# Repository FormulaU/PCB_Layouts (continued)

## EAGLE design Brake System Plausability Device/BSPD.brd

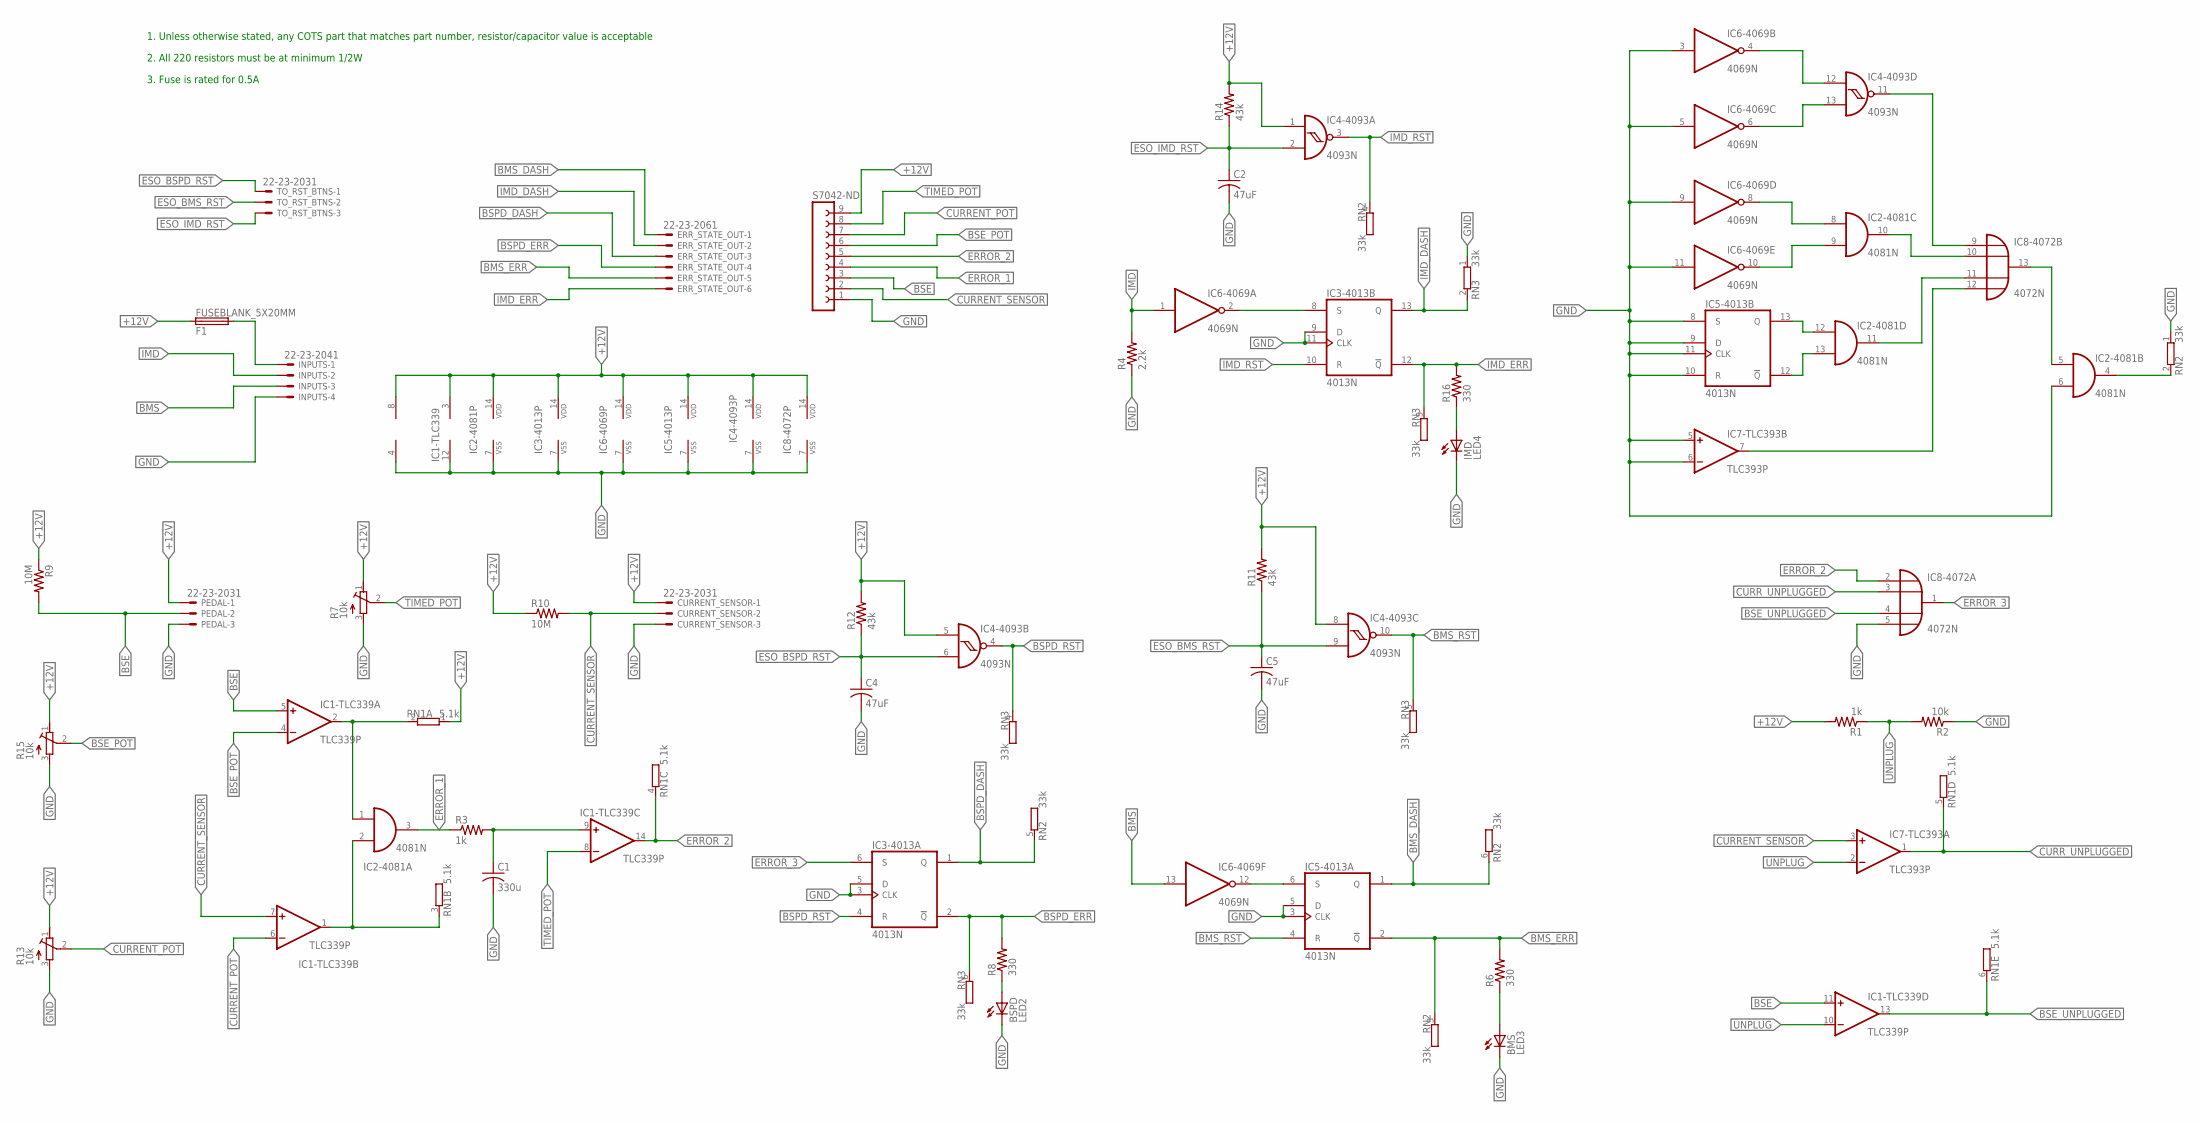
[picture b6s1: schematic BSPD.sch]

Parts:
BMS: LED3; LED3MM
BSPD: LED2; LED3MM
C1: 330u; C225-108X268
C2, C4, C5: 47uF; C050-024X044
CURRENT_SENSOR: 22-23-2031
ERR_STATE_OUT: 22-23-2061
F1: FUSEBLANK_5X20MM; FUSE_HOLDER_5X20MM
IC1-TLC339: TLC339P; DIL14
IC2-4081: 4081N; DIL14
IC3-4013, IC5-4013: 4013N; DIL14
IC4-4093: 4093N; DIL14
IC6-4069: 4069N; DIL14
IC7-TLC393: TLC393P; DIL08
IC8-4072: 4072N; DIL14
IMD: LED4; LED3MM
INPUTS: 22-23-2041
PEDAL: 22-23-2031
R1, R3: 1k; 0207/12
R2: 10k; 0207/12
R4: 2.2k; 0207/12
R6, R8, R16: 330; 0207/12
R7, R13, R15: 10k; RTRIM3006P
R9, R10: 10M; 0207/12
R11, R12, R14: 43k; 0207/12
RN1: 5.1k; SIL6
RN2, RN3: 33k; SIL6
S7042-ND: FE09W
TO_RST_BTNS: 22-23-2031

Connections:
+12V: CURRENT_SENSOR.1, F1.1, IC1-TLC339.3 (V+), IC2-4081.14 (VDD), IC3-4013.14 (VDD), IC4-4093.1 (I0), IC4-4093.5 (I0), IC4-4093.8 (I0), IC4-4093.14 (VDD), IC5-4013.14 (VDD), IC6-4069.14 (VDD), IC7-TLC393.8 (V+), IC8-4072.14 (VDD), PEDAL.1, R1.2, R7.1 (E), R9.1, R10.1, R11.2, R12.2, R13.1 (E), R14.2, R15.1 (E), RN1.1, S7042-ND.9
BMS: IC6-4069.13 (I), INPUTS.3
BMS_DASH: ERR_STATE_OUT.1, IC5-4013.1 (Q), RN2.6 (2)
BMS_ERR: ERR_STATE_OUT.5, IC5-4013.2 (!Q), R6.2, RN2.3 (2)
BMS_RST: IC4-4093.10 (O), IC5-4013.4 (R), RN3.5 (2)
BSE: IC1-TLC339.5 (+IN), IC1-TLC339.11 (+IN), PEDAL.2, R9.2, S7042-ND.3
BSE_POT: IC1-TLC339.4 (-IN), R15.2 (S), S7042-ND.6
BSE_UNPLUGGED: IC1-TLC339.13 (OUT), IC8-4072.4 (I2), RN1.6 (2)
BSPD_DASH: ERR_STATE_OUT.3, IC3-4013.1 (Q), RN2.5 (2)
BSPD_ERR: ERR_STATE_OUT.4, IC3-4013.2 (!Q), R8.2, RN3.6 (2)
BSPD_RST: IC3-4013.4 (R), IC4-4093.4 (O), RN3.4 (2)
CURRENT_POT: IC1-TLC339.6 (-IN), R13.2 (S), S7042-ND.7
CURRENT_SENSOR: CURRENT_SENSOR.2, IC1-TLC339.7 (+IN), IC7-TLC393.3 (+IN), R10.2, S7042-ND.2
CURR_UNPLUGGED: IC7-TLC393.1 (OUT), IC8-4072.3 (I1), RN1.5 (2)
ERROR_1: IC2-4081.3 (O), R3.1, S7042-ND.4
ERROR_2: IC1-TLC339.14 (OUT), IC8-4072.2 (I0), RN1.4 (2), S7042-ND.5
ERROR_3: IC3-4013.6 (S), IC8-4072.1 (O)
ESO_BMS_RST: C5.1, IC4-4093.9 (I1), R11.1, TO_RST_BTNS.2
ESO_BSPD_RST: C4.1, IC4-4093.6 (I1), R12.1, TO_RST_BTNS.1
ESO_IMD_RST: C2.1, IC4-4093.2 (I1), R14.1, TO_RST_BTNS.3
GND: BMS.K (C), BSPD.K (C), C1.2, C2.2, C4.2, C5.2, CURRENT_SENSOR.3, IC1-TLC339.12 (V-), IC2-4081.6 (I1), IC2-4081.7 (VSS), IC3-4013.3 (CLK), IC3-4013.5 (D), IC3-4013.7 (VSS), IC3-4013.9 (D), IC3-4013.11 (CLK), IC4-4093.7 (VSS), IC5-4013.3 (CLK), IC5-4013.5 (D), IC5-4013.7 (VSS), IC5-4013.8 (S), IC5-4013.9 (D), IC5-4013.10 (R), IC5-4013.11 (CLK), IC6-4069.3 (I), IC6-4069.5 (I), IC6-4069.7 (VSS), IC6-4069.9 (I), IC6-4069.11 (I), IC7-TLC393.4 (V-), IC7-TLC393.5 (+IN), IC7-TLC393.6 (-IN), IC8-4072.5 (I3), IC8-4072.7 (VSS), IMD.K (C), INPUTS.4, PEDAL.3, R2.1, R4.1, R7.3 (A), R13.3 (A), R15.3 (A), RN2.1, RN3.1, S7042-ND.1
IMD: IC6-4069.1 (I), INPUTS.2, R4.2
IMD_DASH: ERR_STATE_OUT.2, IC3-4013.13 (Q), RN3.2
IMD_ERR: ERR_STATE_OUT.6, IC3-4013.12 (!Q), R16.2, RN3.3 (2)
IMD_RST: IC3-4013.10 (R), IC4-4093.3 (O), RN2.4 (2)
unnamed: IC1-TLC339.2 (OUT), IC2-4081.1 (I0), RN1.2
unnamed: IC1-TLC339.1 (OUT), IC2-4081.2 (I1), RN1.3 (2)
unnamed: F1.2, INPUTS.1
unnamed: IC3-4013.8 (S), IC6-4069.2 (O)
unnamed: C1.1, IC1-TLC339.9 (+IN), R3.2
unnamed: IC7-TLC393.7 (OUT), IC8-4072.12 (I3)
unnamed: IC4-4093.11 (O), IC8-4072.9 (I0)
unnamed: BMS.A, R6.1
unnamed: IC4-4093.12 (I0), IC6-4069.4 (O)
unnamed: IC2-4081.10 (O), IC8-4072.10 (I1)
unnamed: IC2-4081.11 (O), IC8-4072.11 (I2)
unnamed: IC4-4093.13 (I1), IC6-4069.6 (O)
unnamed: IC5-4013.6 (S), IC6-4069.12 (O)
unnamed: IMD.A, R16.1
unnamed: IC2-4081.9 (I1), IC6-4069.10 (O)
unnamed: IC2-4081.8 (I0), IC6-4069.8 (O)
unnamed: IC2-4081.5 (I0), IC8-4072.13 (O)
unnamed: BSPD.A, R8.1
unnamed: IC2-4081.12 (I0), IC5-4013.13 (Q)
unnamed: IC2-4081.13 (I1), IC5-4013.12 (!Q)
unnamed: IC2-4081.4 (O), RN2.2
TIMED_POT: IC1-TLC339.8 (-IN), R7.2 (S), S7042-ND.8
UNPLUG: IC1-TLC339.10 (-IN), IC7-TLC393.2 (-IN), R1.1, R2.2

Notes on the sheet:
IC1-TLC339
1. Unless otherwise stated, any COTS part that matches part number, resistor/capacitor value is acceptable
2. All 220 resistors must be at minimum 1/2W
3. Fuse is rated for 0.5A

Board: 2 copper layers, 40 parts (0 on the bottom side), 48 nets, no tracks yet.

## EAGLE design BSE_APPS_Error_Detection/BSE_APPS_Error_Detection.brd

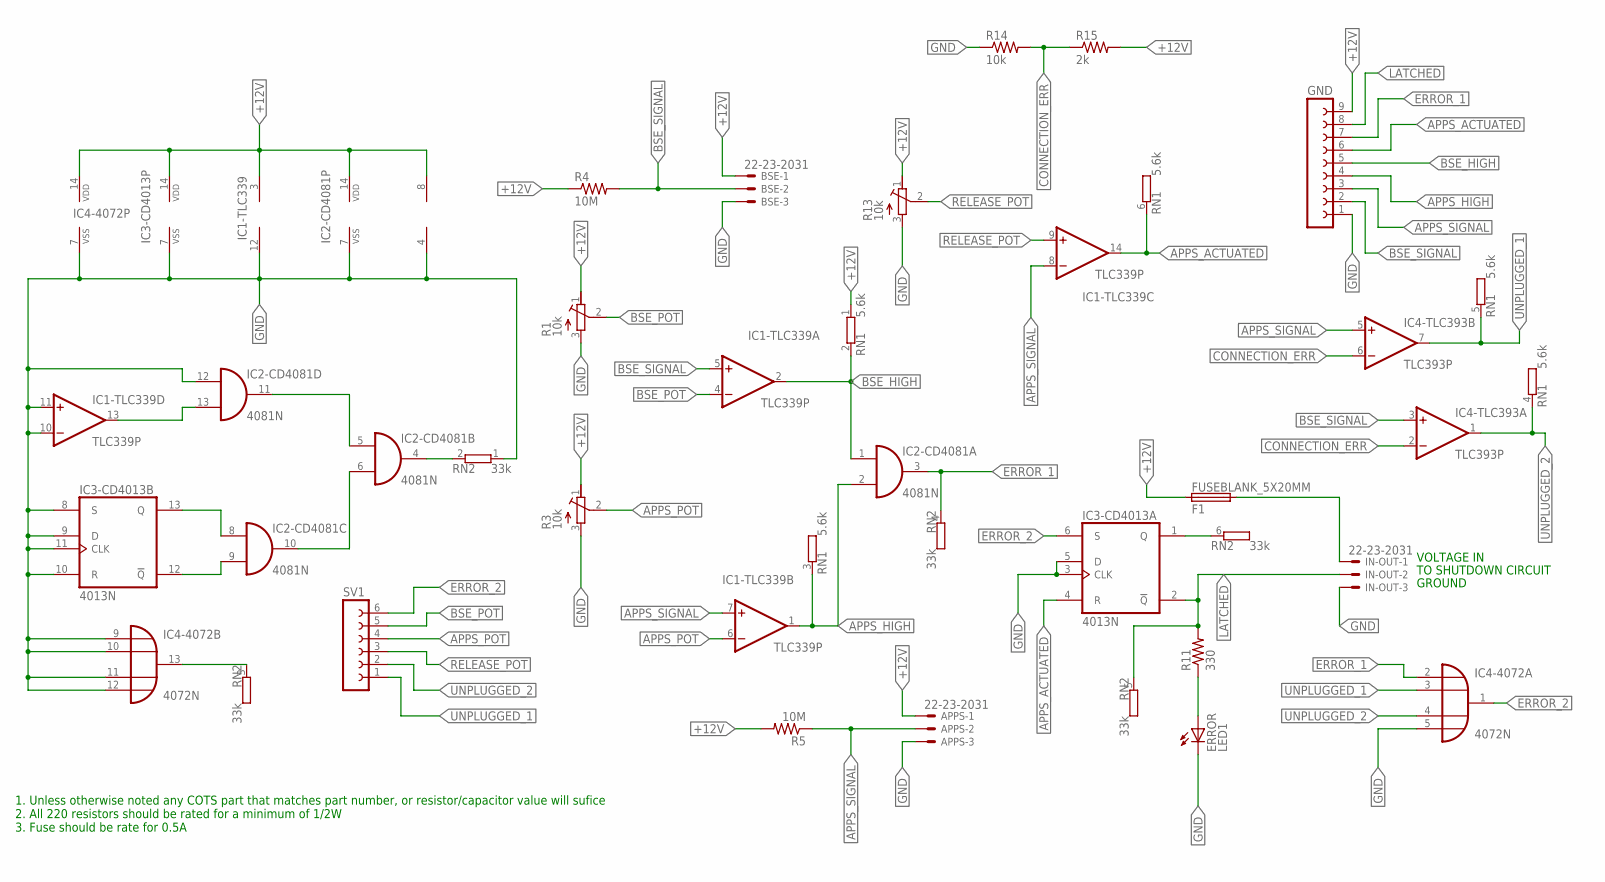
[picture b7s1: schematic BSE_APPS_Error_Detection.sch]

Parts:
APPS: 22-23-2031
BSE: 22-23-2031
ERROR: LED1; LED5MM
F1: FUSEBLANK_5X20MM; FUSE_HOLDER_5X20MM
GND: FE09W
IC1-TLC339: TLC339P; DIL14
IC2-CD4081: 4081N; DIL14
IC3-CD4013: 4013N; DIL14
IC4-4072: 4072N; DIL14
IC4-TLC393: TLC393P; DIL08
IN-OUT: 22-23-2031
R1, R3, R13: 10k; RTRIM3006P
R4, R5: 10M; 0207/10
R11: 330; 0207/10
R14: 10k; 0207/10
R15: 2k; 0207/10
RN1: 5.6k; SIL6
RN2: 33k; SIL6
SV1: FE06W

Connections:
+12V: APPS.1, BSE.1, F1.1, GND.9, IC1-TLC339.3 (V+), IC2-CD4081.14 (VDD), IC3-CD4013.14 (VDD), IC4-4072.14 (VDD), IC4-TLC393.8 (V+), R1.1 (E), R3.1 (E), R4.1, R5.2, R13.1 (E), R15.2, RN1.1
APPS_ACTUATED: GND.6, IC1-TLC339.14 (OUT), IC3-CD4013.4 (R), RN1.6 (2)
APPS_HIGH: GND.4, IC1-TLC339.1 (OUT), IC2-CD4081.2 (I1), RN1.3 (2)
APPS_POT: IC1-TLC339.6 (-IN), R3.2 (S), SV1.4
APPS_SIGNAL: APPS.2, GND.3, IC1-TLC339.7 (+IN), IC1-TLC339.8 (-IN), IC4-TLC393.5 (+IN), R5.1
BSE_HIGH: GND.5, IC1-TLC339.2 (OUT), IC2-CD4081.1 (I0), RN1.2
BSE_POT: IC1-TLC339.4 (-IN), R1.2 (S), SV1.5
BSE_SIGNAL: BSE.2, GND.2, IC1-TLC339.5 (+IN), IC4-TLC393.3 (+IN), R4.2
CONNECTION_ERR: IC4-TLC393.2 (-IN), IC4-TLC393.6 (-IN), R14.2, R15.1
ERROR_1: GND.7, IC2-CD4081.3 (O), IC4-4072.2 (I0), RN2.4 (2)
ERROR_2: IC3-CD4013.6 (S), IC4-4072.1 (O), SV1.6
GND: APPS.3, BSE.3, ERROR.K (C), GND.1, IC1-TLC339.10 (-IN), IC1-TLC339.11 (+IN), IC1-TLC339.12 (V-), IC2-CD4081.7 (VSS), IC2-CD4081.12 (I0), IC3-CD4013.3 (CLK), IC3-CD4013.5 (D), IC3-CD4013.7 (VSS), IC3-CD4013.8 (S), IC3-CD4013.9 (D), IC3-CD4013.10 (R), IC3-CD4013.11 (CLK), IC4-4072.5 (I3), IC4-4072.7 (VSS), IC4-4072.9 (I0), IC4-4072.10 (I1), IC4-4072.11 (I2), IC4-4072.12 (I3), IC4-TLC393.4 (V-), IN-OUT.3, R1.3 (A), R3.3 (A), R13.3 (A), R14.1, RN2.1
LATCHED: GND.8, IC3-CD4013.2 (!Q), IN-OUT.2, R11.2, RN2.5 (2)
unnamed: IC2-CD4081.6 (I1), IC2-CD4081.10 (O)
unnamed: IC1-TLC339.13 (OUT), IC2-CD4081.13 (I1)
unnamed: IC3-CD4013.1 (Q), RN2.6 (2)
unnamed: F1.2, IN-OUT.1
unnamed: IC2-CD4081.8 (I0), IC3-CD4013.13 (Q)
unnamed: ERROR.A, R11.1
unnamed: IC2-CD4081.9 (I1), IC3-CD4013.12 (!Q)
unnamed: IC2-CD4081.5 (I0), IC2-CD4081.11 (O)
unnamed: IC2-CD4081.4 (O), RN2.2
unnamed: IC4-4072.13 (O), RN2.3 (2)
RELEASE_POT: IC1-TLC339.9 (+IN), R13.2 (S), SV1.3
UNPLUGGED_1: IC4-4072.3 (I1), IC4-TLC393.7 (OUT), RN1.5 (2), SV1.1
UNPLUGGED_2: IC4-4072.4 (I2), IC4-TLC393.1 (OUT), RN1.4 (2), SV1.2

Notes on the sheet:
TO SHUTDOWN CIRCUIT
VOLTAGE IN
GROUND
IC1-TLC339
1. Unless otherwise noted any COTS part that matches part number, or resistor/capacitor value will sufice 2. All 220 resistors should be rated for a minimum of 1/2W 3. Fuse should be rate for 0.5A

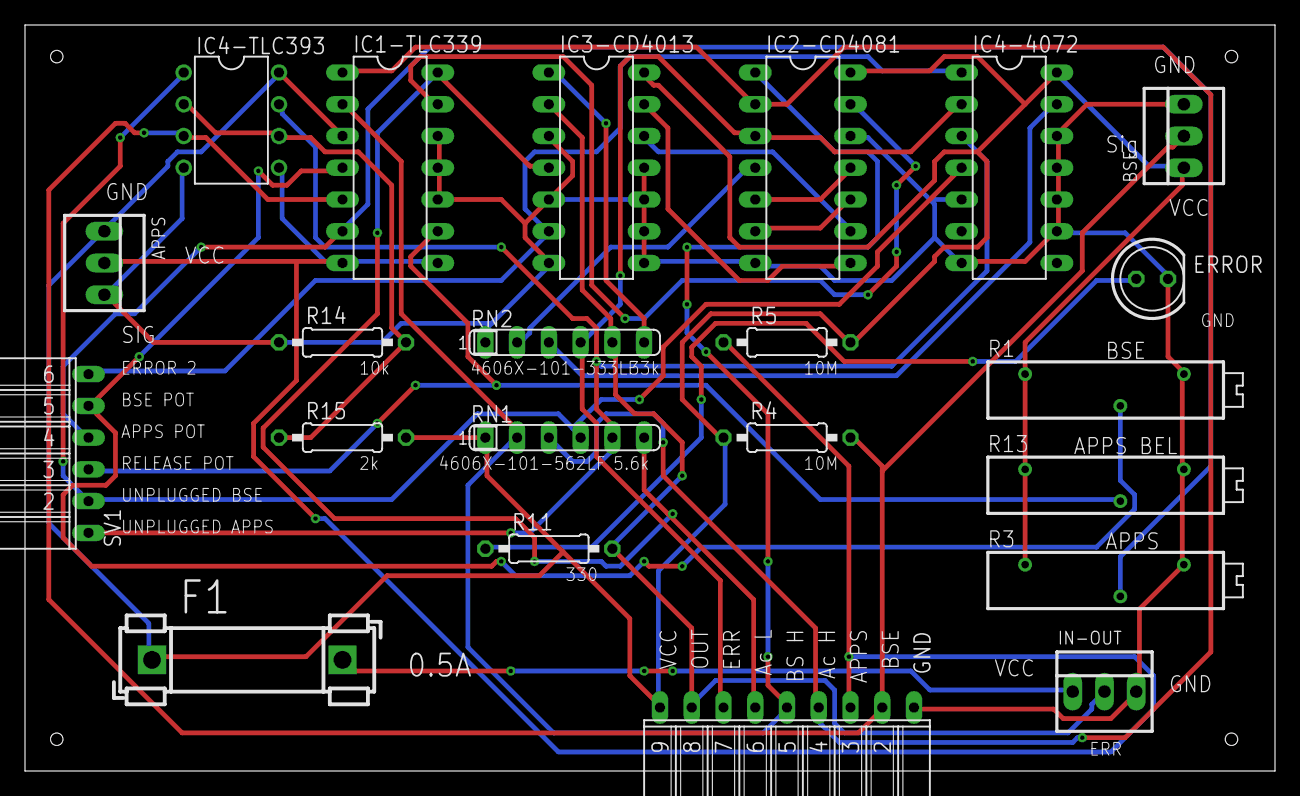
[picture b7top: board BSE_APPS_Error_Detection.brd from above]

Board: 2 copper layers, 100.0 x 59.7 mm, 22 parts (0 on the bottom side), 26 nets.

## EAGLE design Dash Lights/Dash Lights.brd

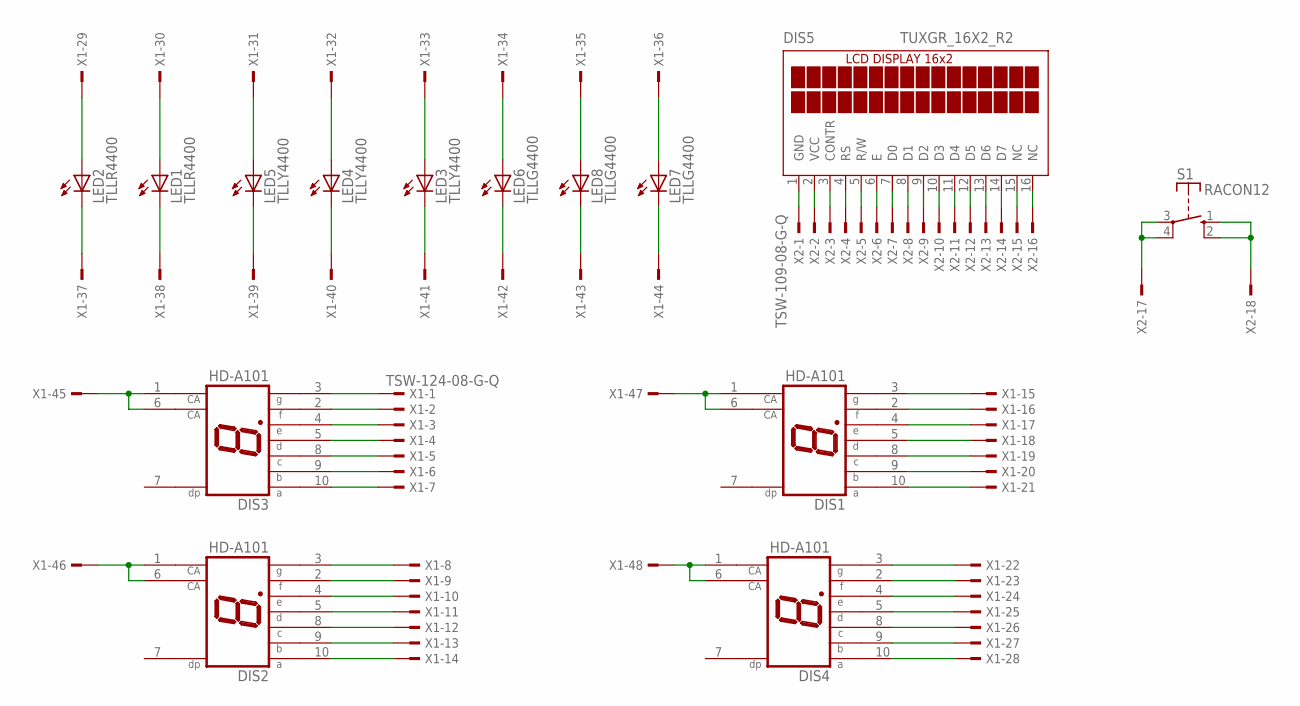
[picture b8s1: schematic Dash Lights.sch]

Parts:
DIS1, DIS2, DIS3, DIS4: HD-A101; HDSP-A
DIS5: TUXGR_16X2_R2
LED1, LED2: TLLR4400; LED3MM
LED3, LED4, LED5: TLLY4400; LED3MM
LED6, LED7, LED8: TLLG4400; LED3MM
S1: RACON12
X1: TSW-124-08-G-Q; TSW-124-XX-G-Q
X2: TSW-109-08-G-Q; TSW-109-XX-G-Q

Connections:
unnamed: DIS3.3 (G), X1.1
unnamed: DIS3.2 (F), X1.2
unnamed: DIS3.4 (E), X1.3
unnamed: DIS3.5 (D), X1.4
unnamed: DIS3.8 (C), X1.5
unnamed: DIS3.9 (B), X1.6
unnamed: DIS3.10 (A), X1.7
unnamed: DIS2.3 (G), X1.8
unnamed: DIS2.2 (F), X1.9
unnamed: DIS2.4 (E), X1.10
unnamed: DIS2.5 (D), X1.11
unnamed: DIS2.8 (C), X1.12
unnamed: DIS2.9 (B), X1.13
unnamed: DIS2.10 (A), X1.14
unnamed: DIS1.3 (G), X1.15
unnamed: DIS1.2 (F), X1.16
unnamed: DIS1.4 (E), X1.17
unnamed: DIS1.5 (D), X1.18
unnamed: DIS1.8 (C), X1.19
unnamed: DIS1.9 (B), X1.20
unnamed: DIS1.10 (A), X1.21
unnamed: DIS4.3 (G), X1.22
unnamed: DIS4.2 (F), X1.23
unnamed: DIS4.4 (E), X1.24
unnamed: DIS4.5 (D), X1.25
unnamed: DIS4.8 (C), X1.26
unnamed: DIS4.9 (B), X1.27
unnamed: DIS4.10 (A), X1.28
unnamed: LED2.A, X1.29
unnamed: LED2.K (C), X1.37
unnamed: LED1.K (C), X1.38
unnamed: LED1.A, X1.30
unnamed: LED5.A, X1.31
unnamed: LED5.K (C), X1.39
unnamed: LED4.A, X1.32
unnamed: LED4.K (C), X1.40
unnamed: LED3.K (C), X1.41
unnamed: LED3.A, X1.33
unnamed: LED6.A, X1.34
unnamed: LED6.K (C), X1.42
unnamed: LED8.K (C), X1.43
unnamed: LED7.K (C), X1.44
unnamed: LED7.A, X1.36
unnamed: LED8.A, X1.35
unnamed: DIS3.1 (CA), DIS3.6 (CA), X1.45
unnamed: DIS2.1 (CA), DIS2.6 (CA), X1.46
unnamed: DIS1.1 (CA), DIS1.6 (CA), X1.47
unnamed: DIS5.1 (GND), X2.1
unnamed: DIS5.2 (VCC), X2.2
unnamed: DIS5.3 (CONTR), X2.3
unnamed: DIS4.1 (CA), DIS4.6 (CA), X1.48
unnamed: DIS5.4 (RS), X2.4
unnamed: DIS5.5 (R/W), X2.5
unnamed: DIS5.6 (E), X2.6
unnamed: DIS5.7 (D0), X2.7
unnamed: DIS5.8 (D1), X2.8
unnamed: DIS5.9 (D2), X2.9
unnamed: DIS5.10 (D3), X2.10
unnamed: DIS5.11 (D4), X2.11
unnamed: DIS5.12 (D5), X2.12
unnamed: DIS5.13 (D6), X2.13
unnamed: DIS5.14 (D7), X2.14
unnamed: DIS5.15 (NC), X2.15
unnamed: DIS5.16 (NC), X2.16
unnamed: S1.3, S1.4, X2.17
unnamed: S1.1 (S), S1.2 (S), X2.18

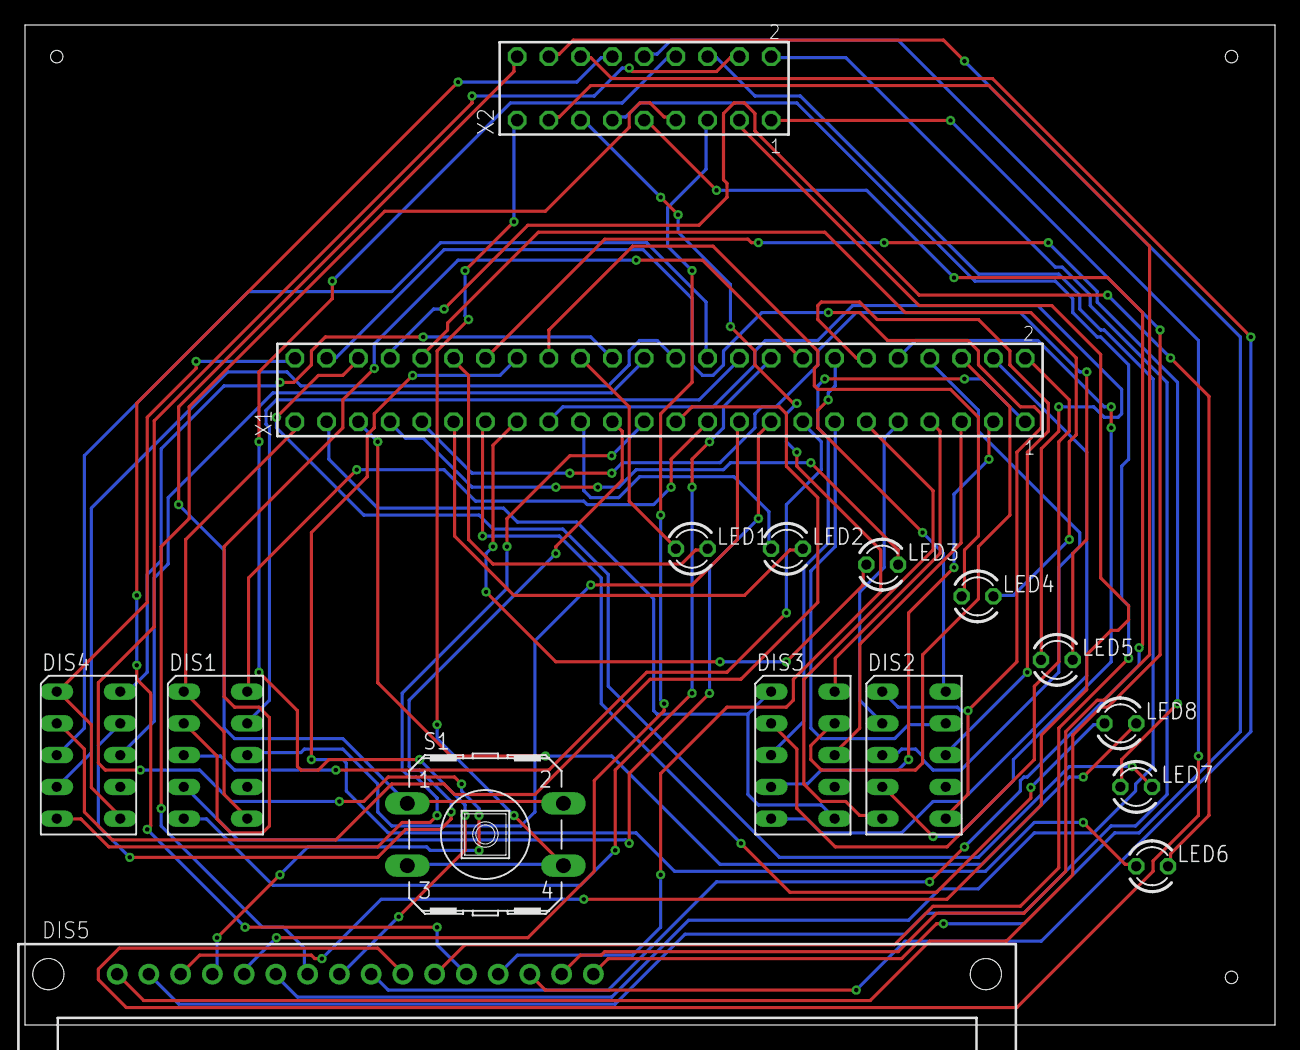
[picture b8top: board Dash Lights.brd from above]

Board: 2 copper layers, 100.0 x 80.0 mm, 16 parts (0 on the bottom side), 66 nets.

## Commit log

2018-01-20 Teensy Baseboard Starting Point
    Read the title ya dingus
2018-01-21 Added Arduino Pro Mini 328 files, SparkFun CAM and design rules, and the Gerber files I used for the first run of the Arduino Pro Minis.
2018-01-28 Some cleanup, added Arduino Pro Mini as a placeholder for the data collectors
2018-01-29 Made 328_data_collector project, defined mezzanine connection.
2018-02-08 More work on 328 schematic. Culled regulator. Left decoupling caps, pretty sure they're overkill though. Consult Brandon and Kirby.
2018-02-25 Updated submodule URL
2018-03-04 Added brandon's circuits
2018-03-06 Brandon
    Brandon
2018-03-16 Teensy
    Teensy fixes
2018-03-16 PCB Designs
    Rev C
2019-01-11 Re-arranged folders, built segment diagram
2019-05-16 Accumulator schematic first pass
2019-05-16 Brandon update.
2020-01-14 New Eagle version
    Also patched attributes to treat schematics as binaries rather than
    text, so we don't show them in diffs.
2020-02-06 BeeMS Common Mezzanine V1 almost done
    Committing just in case the autorouter lights my layout on fire and
    pushes it down the stairs.
2020-02-15 BeeMS Common Daughterboard V0.0.1
2020-02-27 Added BOM for the nucleo common daughterboard
2020-02-27 Screwdown injector V0.0.1
2020-03-19 Added U of U Logo
2021-11-13 Files from Virtual Machine
